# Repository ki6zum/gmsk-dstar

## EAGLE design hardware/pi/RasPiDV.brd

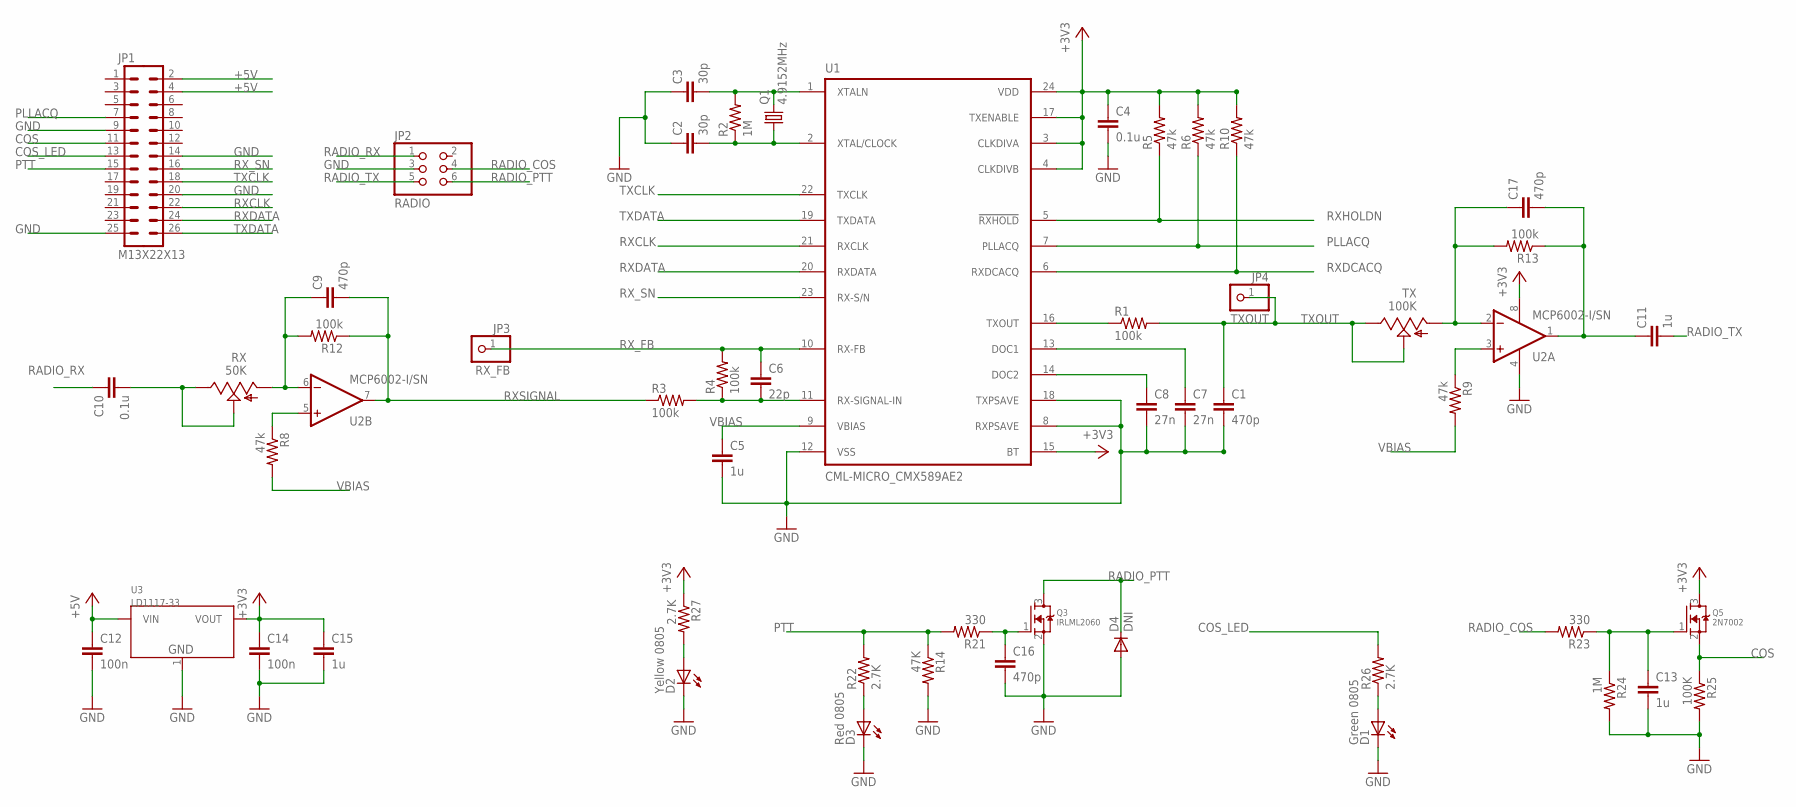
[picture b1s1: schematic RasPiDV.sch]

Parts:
C1, C9, C16, C17: 470p; C0805
C2, C3: 30p; C0805
C4, C10: 0.1u; C0805
C5, C11, C13, C15: 1u; C0805
C6: 22p; C0805
C7, C8: 27n; C0805
C12, C14: 100n; C0805
D1: Green 0805; CHIPLED_0805
D2: Yellow 0805; CHIPLED_0805
D3: Red 0805; CHIPLED_0805
D4: DNI; MICROMELF-R
JP1: M13X22X13; 2X13
JP2: RADIO; 2X03_ROUND_70MIL
JP3: RX_FB; 1X01_ROUND
JP4: TXOUT; 1X01_ROUND
Q1: 4.9152MHz; CRYSTAL_HC49/S
Q3: IRLML2060; SOT23
Q5: 2N7002; SOT23-R
R1, R3, R4, R12, R13: 100k; R0805W
R2, R24: 1M; R0805W
R5, R6, R8, R9, R10: 47k; R0805W
R14: 47K; R0805W
R21, R23: 330; R0805W
R22, R26, R27: 2.7K; R0805W
R25: 100K; R0805W
RX: 50K; B25P
TX: 100K; B25P
U1: CML-MICRO_CMX589AE2; AIS_MK2_CML-MICRO_TSSOP24
U2: MCP6002-I/SN; SOIC-8
U3: LD1117-33; SOT223

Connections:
+3V3: C4.1, C14.1, C15.1, Q5.3 (D), R5.2, R6.2, R10.2, R27.1, U1.3 (CLKDIVA), U1.4 (CLKDIVB), U1.15 (BT), U1.17 (TXENABLE), U1.24 (VDD), U2.8 (V+), U3.2 (VOUT)
+5V: C12.1, JP1.2, JP1.4, U3.3 (VIN)
COS: JP1.11, Q5.2 (S), R25.1
COS_LED: JP1.13, R26.2
GND: C1.2, C2.1, C3.1, C4.2, C5.2, C7.2, C8.2, C12.2, C13.2, C14.2, C15.2, C16.2, D1.C, D2.C, D3.C, D4.A, JP1.9, JP1.14, JP1.20, JP1.25, JP2.3, Q3.2 (S), R14.2, R24.2, R25.2, U1.8 (RXPSAVE), U1.12 (VSS), U1.18 (TXPSAVE), U2.4 (V-), U3.1 (GND)
unnamed: C13.1, Q5.1 (G), R23.1, R24.1
unnamed: D1.A, R26.1
unnamed: C10.2, RX.E, RX.S
unnamed: C8.1, U1.14 (DOC2)
unnamed: C7.1, U1.13 (DOC1)
unnamed: C6.2, R3.2, R4.1, U1.11 (RX-SIGNAL-IN)
unnamed: C9.1, R12.2, RX.A, U2.6 (IN-)
unnamed: C2.2, Q1.1, R2.1, U1.2 (XTAL/CLOCK)
unnamed: C3.2, Q1.2, R2.2, U1.1 (XTALN)
unnamed: R8.1, U2.5 (IN+)
unnamed: R1.1, U1.16 (TXOUT)
unnamed: C11.1, C17.2, R13.1, U2.1 (OUT)
unnamed: D2.A, R27.2
unnamed: R9.1, U2.3 (IN+)
unnamed: C16.1, Q3.1 (G), R21.1
unnamed: C17.1, R13.2, TX.A, U2.2 (IN-)
unnamed: D3.A, R22.1
PLLACQ: JP1.7, R6.1, U1.7 (PLLACQ)
PTT: JP1.15, R14.1, R21.2, R22.2
RADIO_COS: JP2.4, R23.2
RADIO_PTT: D4.C, JP2.6, Q3.3 (D)
RADIO_RX: C10.1, JP2.1
RADIO_TX: C11.2, JP2.5
RXCLK: JP1.22, U1.21 (RXCLK)
RXDATA: JP1.24, U1.20 (RXDATA)
RXDCACQ: R10.1, U1.6 (RXDCACQ)
RXHOLDN: R5.1, U1.5 (!RXHOLD!)
RXSIGNAL: C9.2, R3.1, R12.1, U2.7 (OUT)
RX_FB: C6.1, JP3.1, R4.2, U1.10 (RX-FB)
RX_SN: JP1.16, U1.23 (RX-S/N)
TXCLK: JP1.18, U1.22 (TXCLK)
TXDATA: JP1.26, U1.19 (TXDATA)
TXOUT: C1.1, JP4.1, R1.2, TX.E, TX.S
VBIAS: C5.1, R8.2, R9.2, U1.9 (VBIAS)

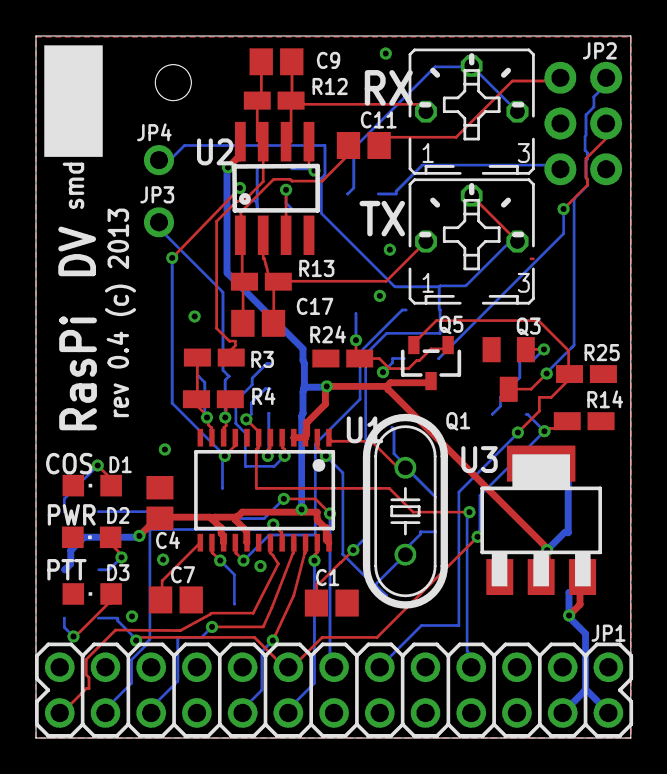
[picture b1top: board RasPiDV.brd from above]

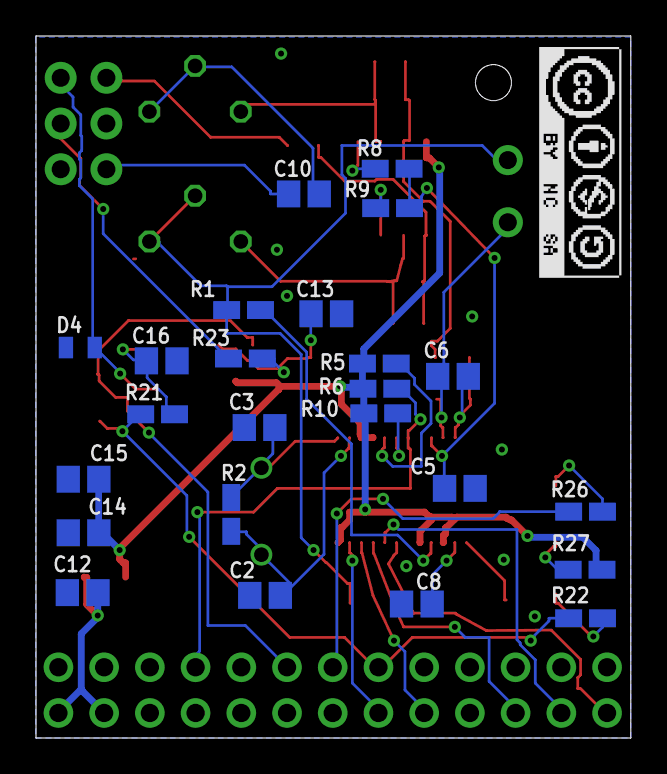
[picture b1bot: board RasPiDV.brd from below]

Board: 2 copper layers, 33.0 x 39.0 mm, 52 parts (24 on the bottom side), 39 nets.

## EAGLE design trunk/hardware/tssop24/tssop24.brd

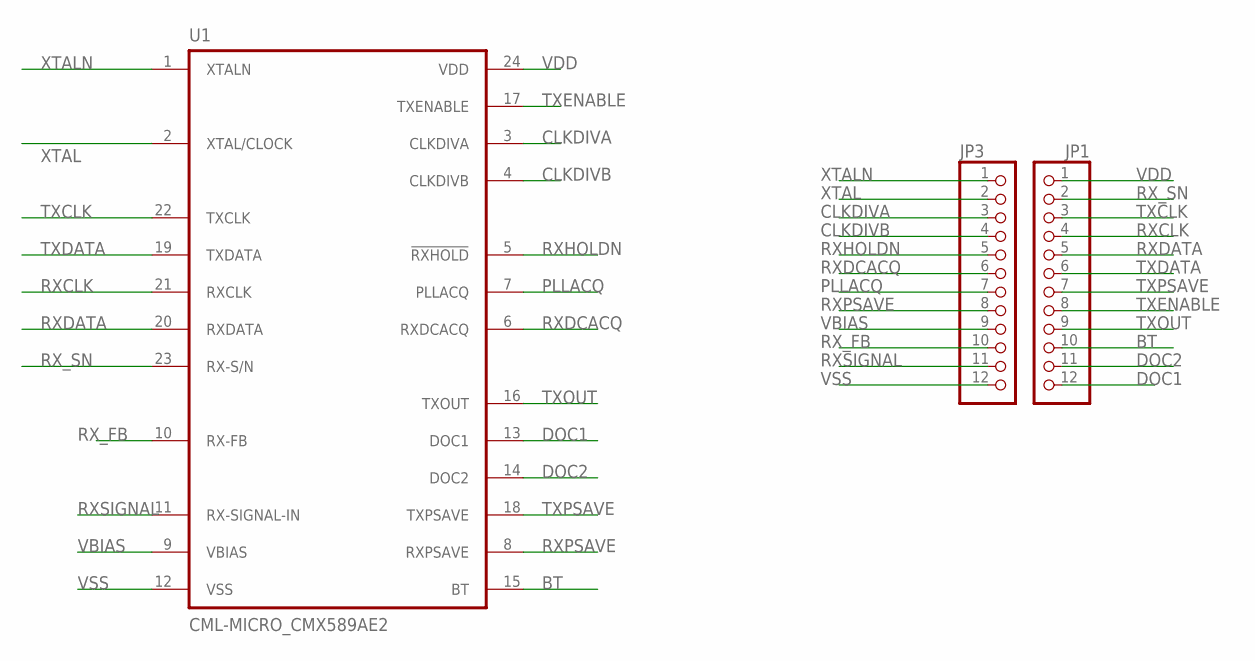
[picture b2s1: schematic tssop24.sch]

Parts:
JP1, JP3: PINHD-1X12-CB; 1X12-CB
U1: CML-MICRO_CMX589AE2; AIS_MK2_CML-MICRO_TSSOP24

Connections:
BT: JP1.10, U1.15 (BT)
CLKDIVA: JP3.3, U1.3 (CLKDIVA)
CLKDIVB: JP3.4, U1.4 (CLKDIVB)
DOC1: JP1.12, U1.13 (DOC1)
DOC2: JP1.11, U1.14 (DOC2)
PLLACQ: JP3.7, U1.7 (PLLACQ)
RXCLK: JP1.4, U1.21 (RXCLK)
RXDATA: JP1.5, U1.20 (RXDATA)
RXDCACQ: JP3.6, U1.6 (RXDCACQ)
RXHOLDN: JP3.5, U1.5 (!RXHOLD!)
RXPSAVE: JP3.8, U1.8 (RXPSAVE)
RXSIGNAL: JP3.11, U1.11 (RX-SIGNAL-IN)
RX_FB: JP3.10, U1.10 (RX-FB)
RX_SN: JP1.2, U1.23 (RX-S/N)
TXCLK: JP1.3, U1.22 (TXCLK)
TXDATA: JP1.6, U1.19 (TXDATA)
TXENABLE: JP1.8, U1.17 (TXENABLE)
TXOUT: JP1.9, U1.16 (TXOUT)
TXPSAVE: JP1.7, U1.18 (TXPSAVE)
VBIAS: JP3.9, U1.9 (VBIAS)
VDD: JP1.1, U1.24 (VDD)
VSS: JP3.12, U1.12 (VSS)
XTAL: JP3.2, U1.2 (XTAL/CLOCK)
XTALN: JP3.1, U1.1 (XTALN)

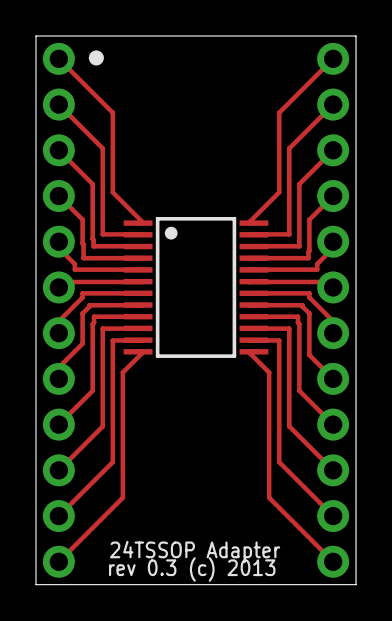
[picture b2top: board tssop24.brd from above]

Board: 2 copper layers, 17.8 x 30.5 mm, 3 parts (0 on the bottom side), 24 nets.

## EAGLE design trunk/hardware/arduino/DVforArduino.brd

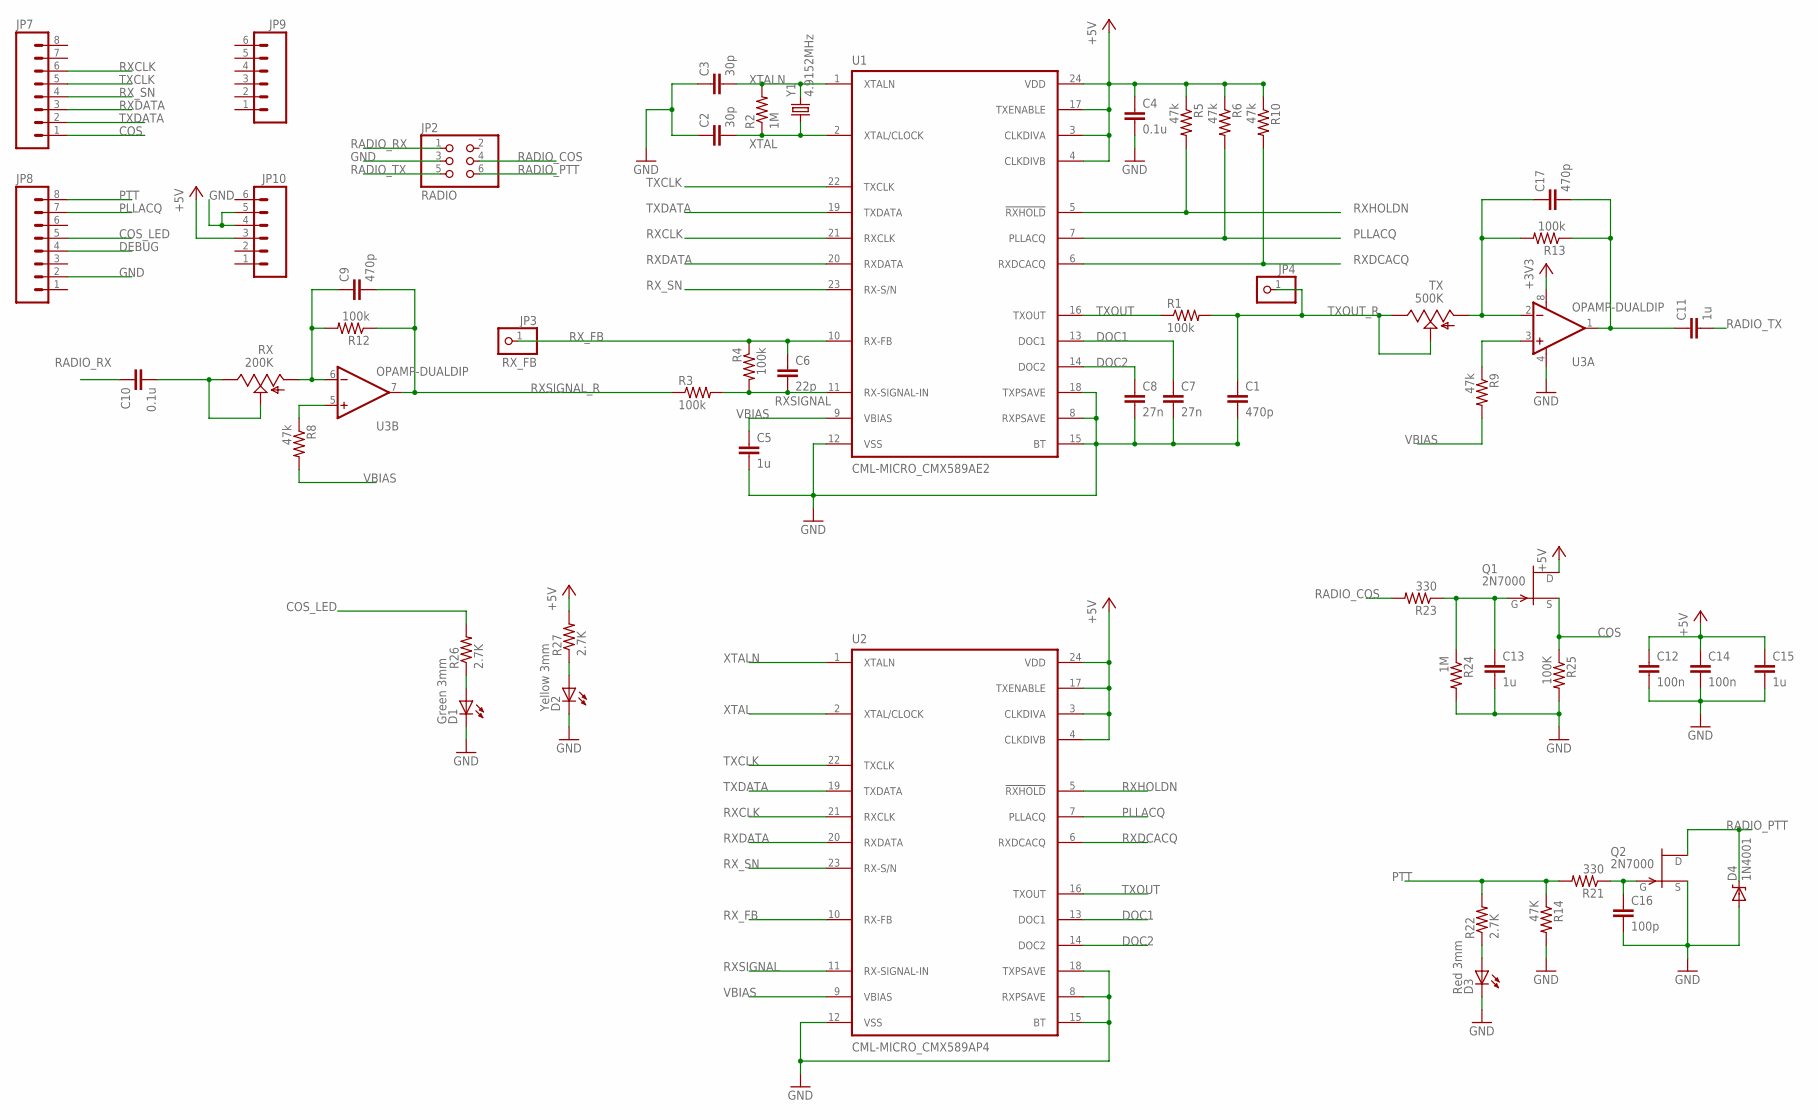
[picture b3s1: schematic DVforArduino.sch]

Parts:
C1, C9, C17: 470p; C2.5-3
C2, C3: 30p; C2.5-3
C4, C10: 0.1u; C2.5-3
C5, C11, C13, C15: 1u; C2.5-3
C6: 22p; C2.5-3
C7, C8: 27n; C2.5-3
C12, C14: 100n; C2.5-3
C16: 100p; C2.5-3
D1: Green 3mm; LED3MM
D2: Yellow 3mm; LED3MM
D3: Red 3mm; LED3MM
D4: 1N4001; DIODE-ZENER
JP2: RADIO; 2X03_ROUND_70MIL
JP3: RX_FB; 1X01_ROUND
JP4: HEADER-1X1ROUND; 1X01_ROUND
JP7, JP8: M081X08; 1X08
JP9, JP10: M06SIP; 1X06
Q1, Q2: 2N7000; TO92
R1, R3, R4, R12, R13: 100k; 0204V
R2, R24: 1M; 0204V
R5, R6, R8, R9, R10: 47k; 0204V
R14: 47K; 0204V
R21, R23: 330; 0204V
R22, R26, R27: 2.7K; 0204V
R25: 100K; 0204V
RX: 200K; B25P
TX: 500K; B25P
U1: CML-MICRO_CMX589AE2; AIS_MK2_CML-MICRO_TSSOP24
U2: CML-MICRO_CMX589AP4; AIS_MK2_CML-MICRO_DIL24-6
U3: OPAMP-DUALDIP; DIP08
Y1: 4.9152MHz; HC49US

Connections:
COS: JP7.1, Q1.3 (S), R25.1
COS_LED: JP8.5, R26.2
DEBUG: JP8.4
DOC1: C7.1, U1.13 (DOC1), U2.13 (DOC1)
DOC2: C8.1, U1.14 (DOC2), U2.14 (DOC2)
unnamed: C13.1, Q1.2 (G), R23.1, R24.1
unnamed: D1.A, R26.1
unnamed: C10.2, RX.E, RX.S
unnamed: D2.A, R27.1
unnamed: C9.1, R12.2, RX.A, U3.6 (-IN)
unnamed: R8.1, U3.5 (+IN)
unnamed: C11.1, C17.2, R13.1, U3.1 (OUT)
unnamed: R9.1, U3.3 (+IN)
unnamed: C16.1, Q2.2 (G), R21.1
unnamed: C17.1, R13.2, TX.A, U3.2 (-IN)
unnamed: D3.A, R22.1
PLLACQ: JP8.7, R6.2, U1.7 (PLLACQ), U2.7 (PLLACQ)
PTT: JP8.8, R14.1, R21.2, R22.2
RADIO_COS: JP2.4, R23.2
RADIO_PTT: D4.P$1 (C), JP2.6, Q2.1 (D)
RADIO_RX: C10.1, JP2.1
RADIO_TX: C11.2, JP2.5
RESET: JP10.1; also elsewhere on the board
RXCLK: JP7.6, U1.21 (RXCLK), U2.21 (RXCLK)
RXDATA: JP7.3, U1.20 (RXDATA), U2.20 (RXDATA)
RXDCACQ: R10.2, U1.6 (RXDCACQ), U2.6 (RXDCACQ)
RXHOLDN: R5.2, U1.5 (!RXHOLD!), U2.5 (!RXHOLD!)
RXSIGNAL: C6.2, R3.2, R4.2, U1.11 (RX-SIGNAL-IN), U2.11 (RX-SIGNAL-IN)
RXSIGNAL_R: C9.2, R3.1, R12.1, U3.7 (OUT)
RX_FB: C6.1, JP3.1, R4.1, U1.10 (RX-FB), U2.10 (RX-FB)
RX_SN: JP7.4, U1.23 (RX-S/N), U2.23 (RX-S/N)
TXCLK: JP7.5, U1.22 (TXCLK), U2.22 (TXCLK)
TXDATA: JP7.2, U1.19 (TXDATA), U2.19 (TXDATA)
TXOUT: R1.1, U1.16 (TXOUT), U2.16 (TXOUT)
TXOUT_R: C1.1, JP4.1, R1.2, TX.E, TX.S
VBIAS: C5.1, R8.2, R9.2, U1.9 (VBIAS), U2.9 (VBIAS)
XTAL: C2.2, R2.1, U1.2 (XTAL/CLOCK), U2.2 (XTAL/CLOCK), Y1.1
XTALN: C3.2, R2.2, U1.1 (XTALN), U2.1 (XTALN), Y1.2

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
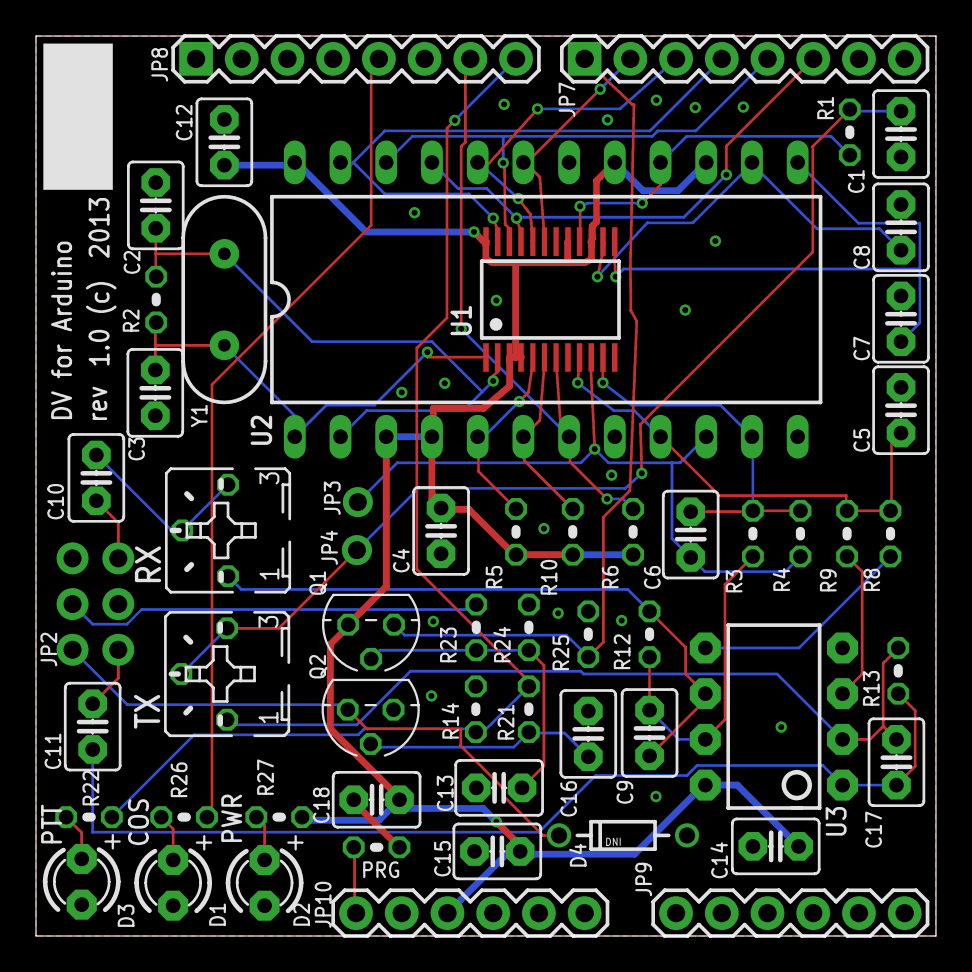
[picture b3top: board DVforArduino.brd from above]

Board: 4 copper layers, 50.0 x 50.0 mm, 57 parts (0 on the bottom side), 40 nets.

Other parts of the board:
C18: 10u; C2.5-3
PRG: DNI; 0204V

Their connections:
unnamed: C18.1, PRG.1
RESET: PRG.2; also elsewhere on the board

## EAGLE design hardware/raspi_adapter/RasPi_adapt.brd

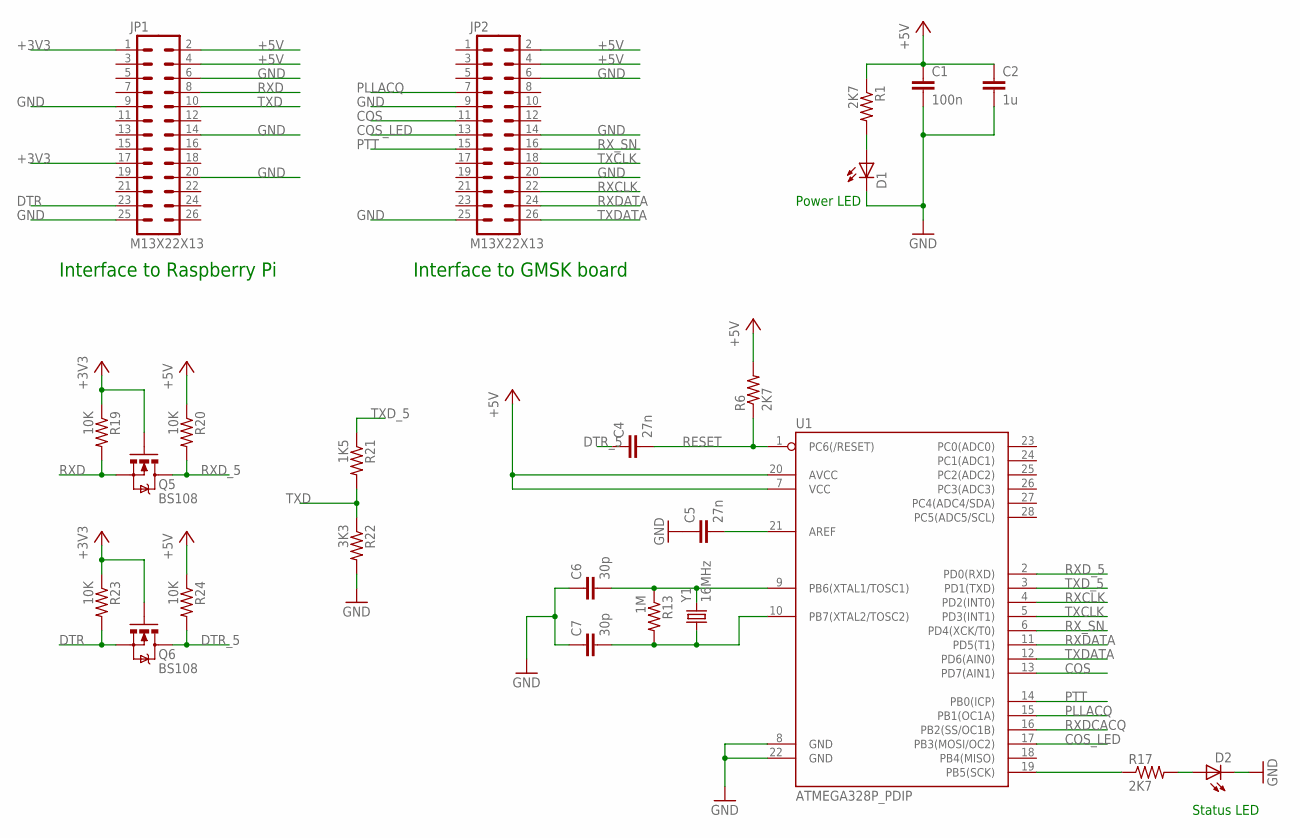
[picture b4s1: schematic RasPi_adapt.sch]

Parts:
C1: 100n; CAP-PTH-SMALLEZ
C2: 1u; CAP-PTH-SMALLEZ
C4, C5: 27n; CAP-PTH-SMALLEZ
C6, C7: 30p; CAP-PTH-SMALLEZ
D1, D2: LED3MM
JP1, JP2: M13X22X13; 2X13
Q5, Q6: BS108; TO-92
R1, R6, R17: 2K7; AXIAL-0.3EZ
R13: 1M; AXIAL-0.3EZ
R19, R20, R23, R24: 10K; AXIAL-0.3EZ
R21: 1K5; AXIAL-0.3EZ
R22: 3K3; AXIAL-0.3EZ
U1: ATMEGA328P_PDIP; DIL28-3
Y1: 16MHz; CRYSTAL_HC49/S

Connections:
+3V3: JP1.1, JP1.17, Q5.2 (G), Q6.2 (G), R19.P$1 (1), R23.P$1 (1)
+5V: C1.1, C2.1, JP1.2, JP1.4, JP2.2, JP2.4, R1.P$1 (1), R6.P$2 (2), R20.P$1 (1), R24.P$1 (1), U1.7 (VCC), U1.20 (AVCC)
COS: JP2.11, U1.13 (PD7(AIN1))
COS_LED: JP2.13, U1.17 (PB3(MOSI/OC2))
DTR: JP1.23, Q6.3 (S), R23.P$2 (2)
DTR_5: C4.1, Q6.1 (D), R24.P$2 (2)
GND: C1.2, C2.2, C5.1, C6.1, C7.1, D1.K (C), D2.K (C), JP1.6, JP1.9, JP1.14, JP1.20, JP1.25, JP2.6, JP2.9, JP2.14, JP2.20, JP2.25, R22.P$2 (2), U1.8 (GND), U1.22 (GND)
unnamed: R17.P$1 (1), U1.19 (PB5(SCK))
unnamed: D1.A, R1.P$2 (2)
unnamed: D2.A, R17.P$2 (2)
unnamed: C7.2, R13.P$2 (2), U1.10 (PB7(XTAL2/TOSC2)), Y1.1
unnamed: C6.2, R13.P$1 (1), U1.9 (PB6(XTAL1/TOSC1)), Y1.2
unnamed: C5.2, U1.21 (AREF)
PLLACQ: JP2.7, U1.15 (PB1(OC1A))
PTT: JP2.15, U1.14 (PB0(ICP))
RESET: C4.2, R6.P$1 (1), U1.1 (PC6(/RESET))
RXCLK: JP2.22, U1.4 (PD2(INT0))
RXD: JP1.8, Q5.3 (S), R19.P$2 (2)
RXDATA: JP2.24, U1.11 (PD5(T1))
RXDCACQ: U1.16 (PB2(SS/OC1B))
RXD_5: Q5.1 (D), R20.P$2 (2), U1.2 (PD0(RXD))
RX_SN: JP2.16, U1.6 (PD4(XCK/T0))
TXCLK: JP2.18, U1.5 (PD3(INT1))
TXD: JP1.10, R21.P$2 (2), R22.P$1 (1)
TXDATA: JP2.26, U1.12 (PD6(AIN0))
TXD_5: R21.P$1 (1), U1.3 (PD1(TXD))

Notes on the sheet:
Status LED
Power LED
Interface to Raspberry Pi
Interface to GMSK board

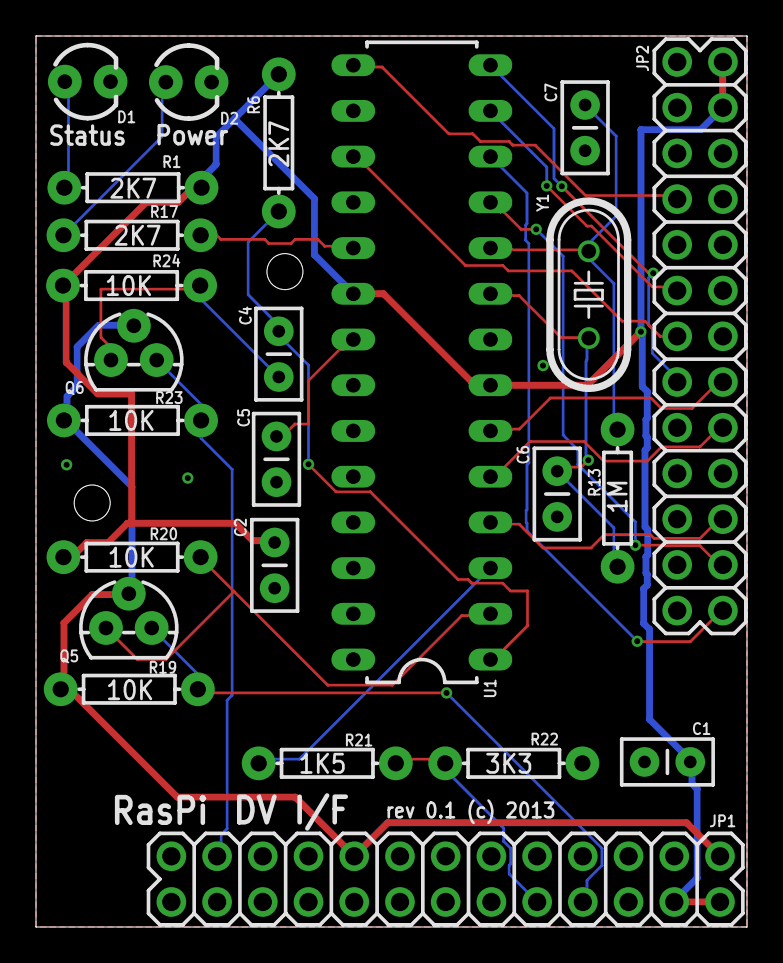
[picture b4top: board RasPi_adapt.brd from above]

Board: 4 copper layers, 39.5 x 49.5 mm, 24 parts (0 on the bottom side), 25 nets.

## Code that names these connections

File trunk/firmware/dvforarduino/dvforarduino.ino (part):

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typedef struct RXFRAME589 {
    uint8_t header;
    uint8_t tx_fifo   : 7; // fifo for data going to 589
    uint8_t cos_pin   : 1;
    uint8_t rx_fifo   : 7; // fifo for data coming from 589
    uint8_t reserved  : 1;
    uint8_t rawbits[RAWSIZE];
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                             }
                        }
                    // handle the PTT, PLLACQ, COSLED and SN_mode settings coming from the host
                    digitalWrite(pinPTT, txtesting.ptt ? HIGH:LOW);
                    digitalWrite(pinPLLACQ, txtesting.pllacq ? HIGH:LOW);
                    digitalWrite(pinCOSLED, txtesting.cosled ? HIGH:LOW);
                    //rxMode = txtesting.sn_mode;
                    
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        
        rxtesting.tx_fifo = TXfifolevel;
        rxtesting.rx_fifo = RXfifolevel;
        rxtesting.cos_pin = digitalRead(pinCOS);
        rxtesting.reserved = 0;
        rxtesting.crc = crc8((uint8_t *)&rxtesting, RAWSIZE+3);
        Serial.write((uint8_t *)&rxtesting, RAWSIZE+4);
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
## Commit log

2015-07-15 Migrating wiki contents from Google Code

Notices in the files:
trunk/firmware/dvforarduino/dvforarduino.ino:
DVforArduino version 0.1 - Copyright (C) 2013
Serial1.println("DVforArduino  Copyright (C) 2013
hardware/pi/RasPiDV.brd:
rev 0.4 (c) 2013
hardware/raspi_adapter/RasPi_adapt.brd:
rev 0.1 (c) 2013
trunk/hardware/tssop24/tssop24.brd:
rev 0.3 (c) 2013
parts and their libraries:
SparkFun-Connectors: Licensing: CC v3.0 Share-Alike You are welcome to use this library for commercial purposes.
microbuilder: This work is placed in the public domain, and may be freely used for commercial and non-commercial work with the following conditions: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
